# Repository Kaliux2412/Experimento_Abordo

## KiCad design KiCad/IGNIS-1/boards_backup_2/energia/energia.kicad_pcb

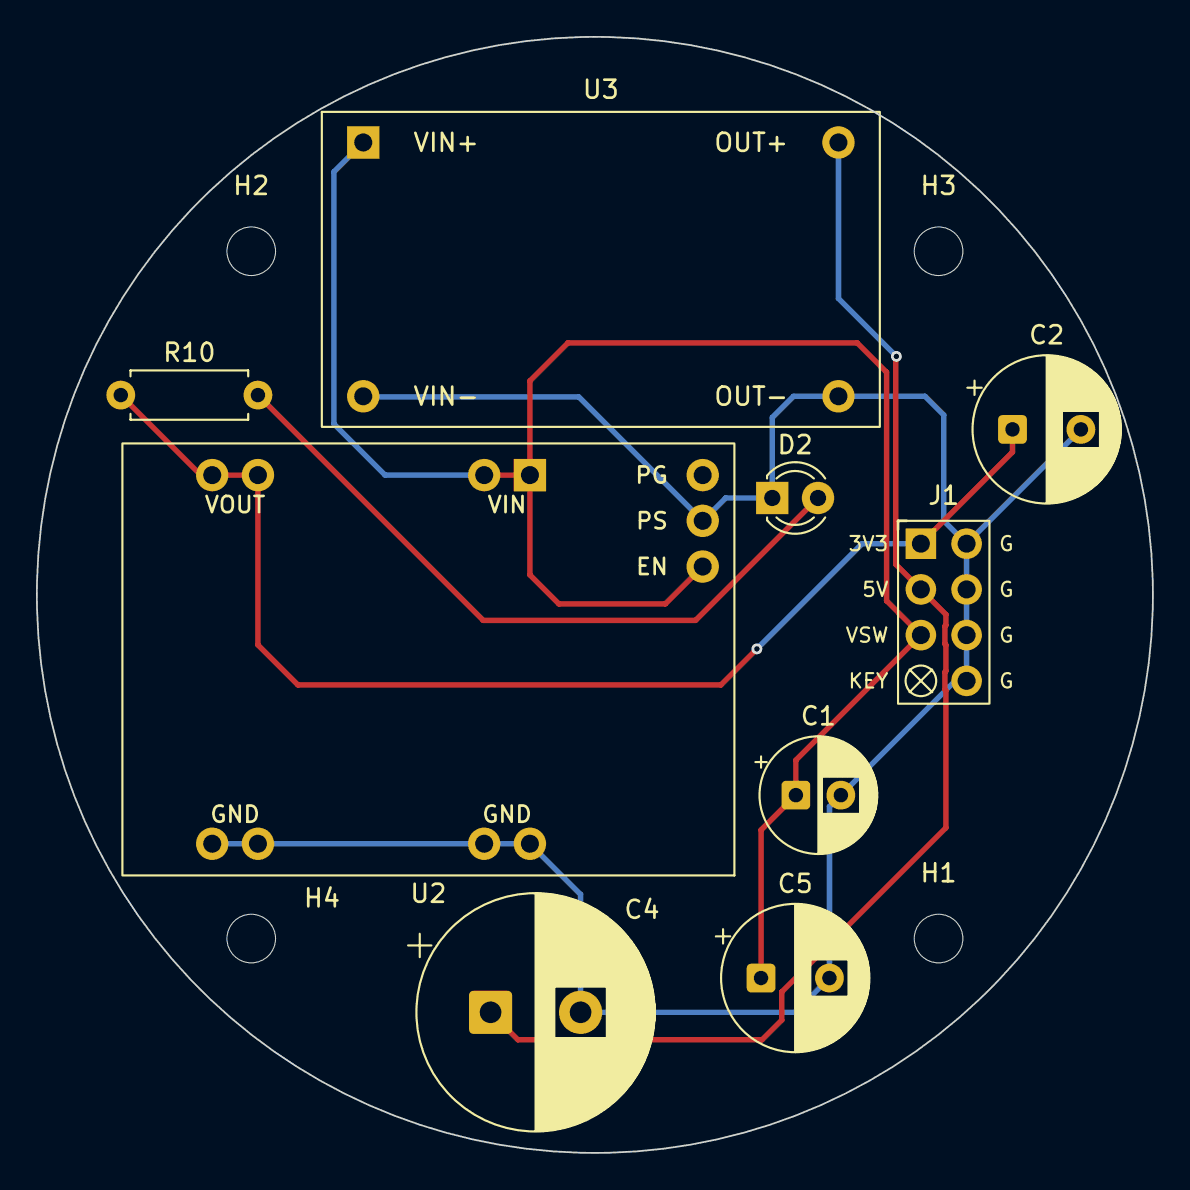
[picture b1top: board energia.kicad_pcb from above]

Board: 2 copper layers, 62.0 x 62.0 mm, 13 parts (0 on the bottom side), 5 nets.

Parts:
C1: 22uF; CP_Radial_D6.3mm_P2.50mm
C2, C5: 100uF; CP_Radial_D8.0mm_P3.80mm
C4: 220uF; CP_Radial_D13.0mm_P5.00mm
D2: PWR_grn; LED_D3.0mm
H1, H2, H3, H4: M2.5_hole; MountingHole_2.7mm_M2.5
J1: J_PWR_2x4; J_PWR_2x4_Keyed
R10: 1k; R_Axial_DIN0207_L6.3mm_D2.5mm_P7.62mm_Horizontal
U2: TPS63020; TPS63020_module
U3: Boost_5V; MT3608_module

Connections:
+3V3: C2.1, J1.1 (+3V3), R10.1, U2.2 (VOUT)
+5V: C4.1, J1.3 (+5V), U3.3 (OUT+)
GND: C1.2, C2.2, C4.2, C5.2, D2.1 (K), J1.2 (GND), J1.4 (GND), J1.6 (GND), J1.8 (GND), U2.3 (GND), U2.5 (PS), U3.2 (VIN-), U3.4 (OUT-)
unnamed: D2.2 (A), R10.2
VSW: C1.1, C5.1, J1.5 (VSW), U2.1 (VIN), U2.4 (EN), U3.1 (VIN+)

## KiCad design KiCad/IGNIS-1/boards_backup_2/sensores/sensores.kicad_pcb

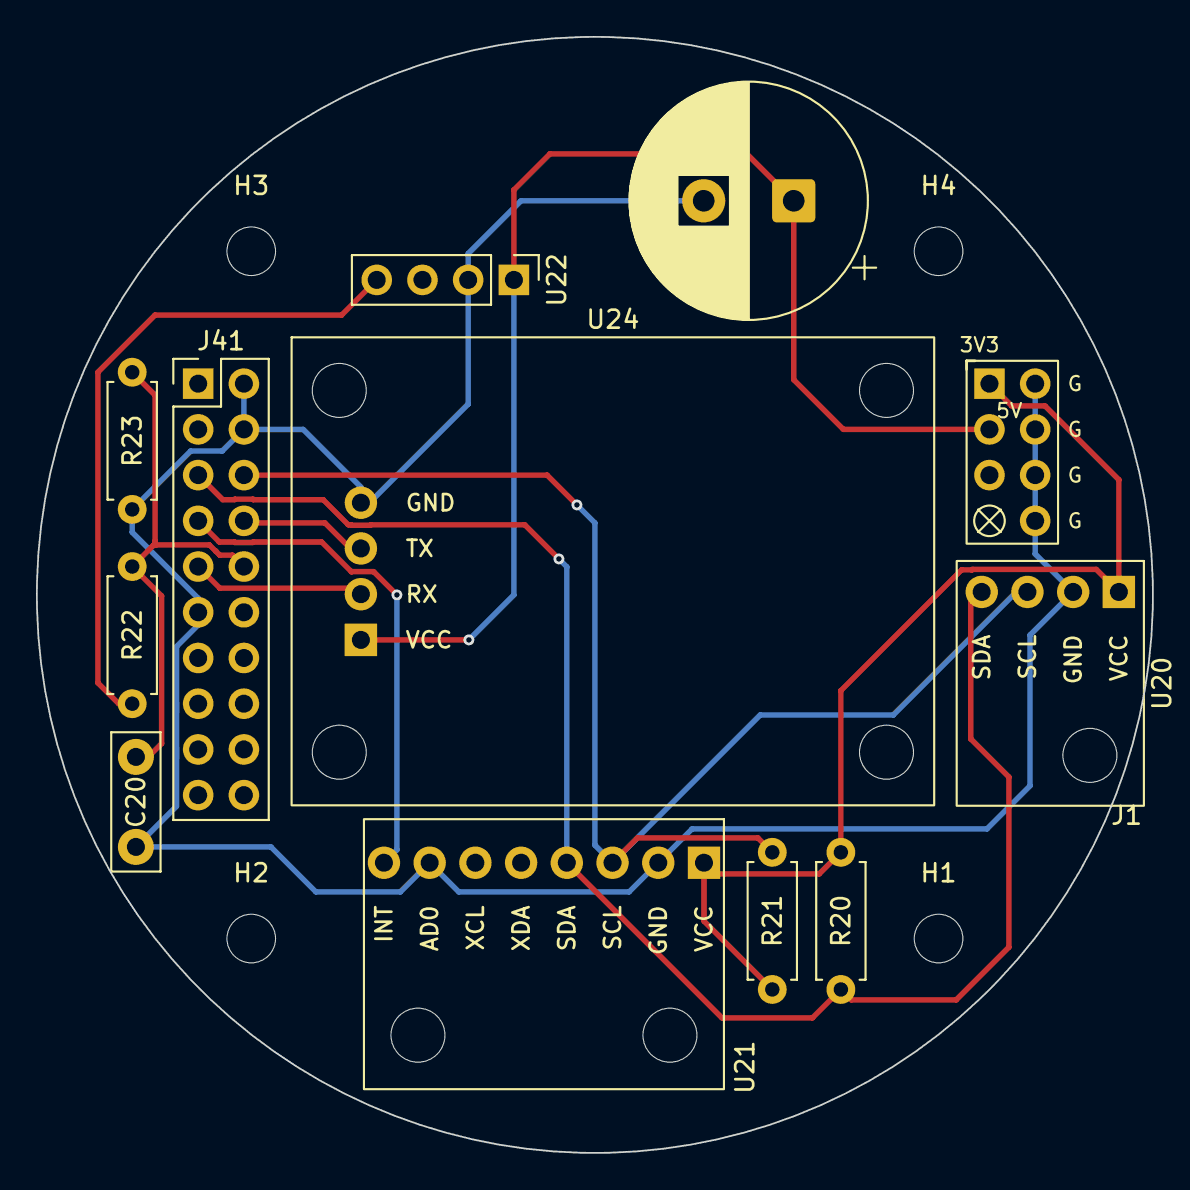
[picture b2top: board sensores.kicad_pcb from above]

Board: 2 copper layers, 62.0 x 62.0 mm, 16 parts (0 on the bottom side), 10 nets.

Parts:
C4: 220uF; CP_Radial_D13.0mm_P5.00mm
C20: 100nF; C_Disc_D7.5mm_W2.5mm_P5.00mm
H1, H2, H3, H4: M2.5_hole; MountingHole_2.7mm_M2.5
J1: J_PWR_2x4; J_PWR_2x4_Keyed
J41: J_DAT; PinHeader_2x10_P2.54mm_Vertical
R20, R21: 4.7k; R_Axial_DIN0207_L6.3mm_D2.5mm_P7.62mm_Horizontal
R22: 10k; R_Axial_DIN0207_L6.3mm_D2.5mm_P7.62mm_Horizontal
R23: 15k; R_Axial_DIN0207_L6.3mm_D2.5mm_P7.62mm_Horizontal
U20: BME280; BME280_module
U21: MPU6050; MPU6050_module
U22: MQ-135; PinHeader_1x04_P2.54mm_Vertical
U24: GPS NEO-6M; GPS_NEO6M_module

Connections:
+3V3: J1.1 (+3V3), R20.1, R21.1, U20.1 (VIN), U21.1 (VCC)
+5V: C4.1, J1.3 (+5V), U22.1 (VCC), U24.1 (VCC)
GND: C4.2, C20.2, J1.2 (GND), J1.4 (GND), J1.6 (GND), J1.8 (GND), J41.2, J41.4, J41.11, R23.2, U20.2 (GND), U21.2 (GND), U21.7 (AD0), U22.2 (GND), U24.4 (GND)
GPS_RX: J41.9, U24.2 (RX)
GPS_TX: J41.8, U24.3 (TX)
MPU_INT: J41.7, U21.8 (INT)
MQ_AOUT: C20.1, J41.10, R22.2, R23.1
unnamed: R22.1, U22.4 (A0)
SCL: J41.6, R21.2, U20.3 (SCL), U21.3 (SCL)
SDA: J41.5, R20.2, U20.4 (SDA), U21.4 (SDA)
